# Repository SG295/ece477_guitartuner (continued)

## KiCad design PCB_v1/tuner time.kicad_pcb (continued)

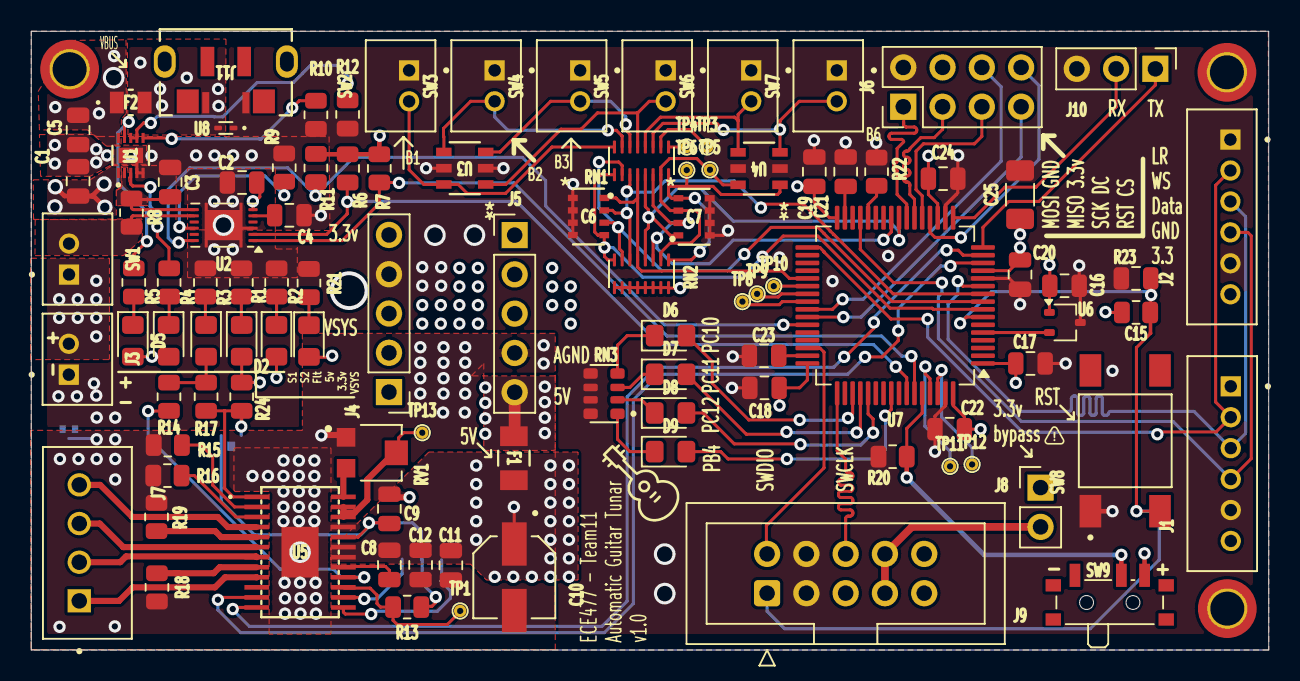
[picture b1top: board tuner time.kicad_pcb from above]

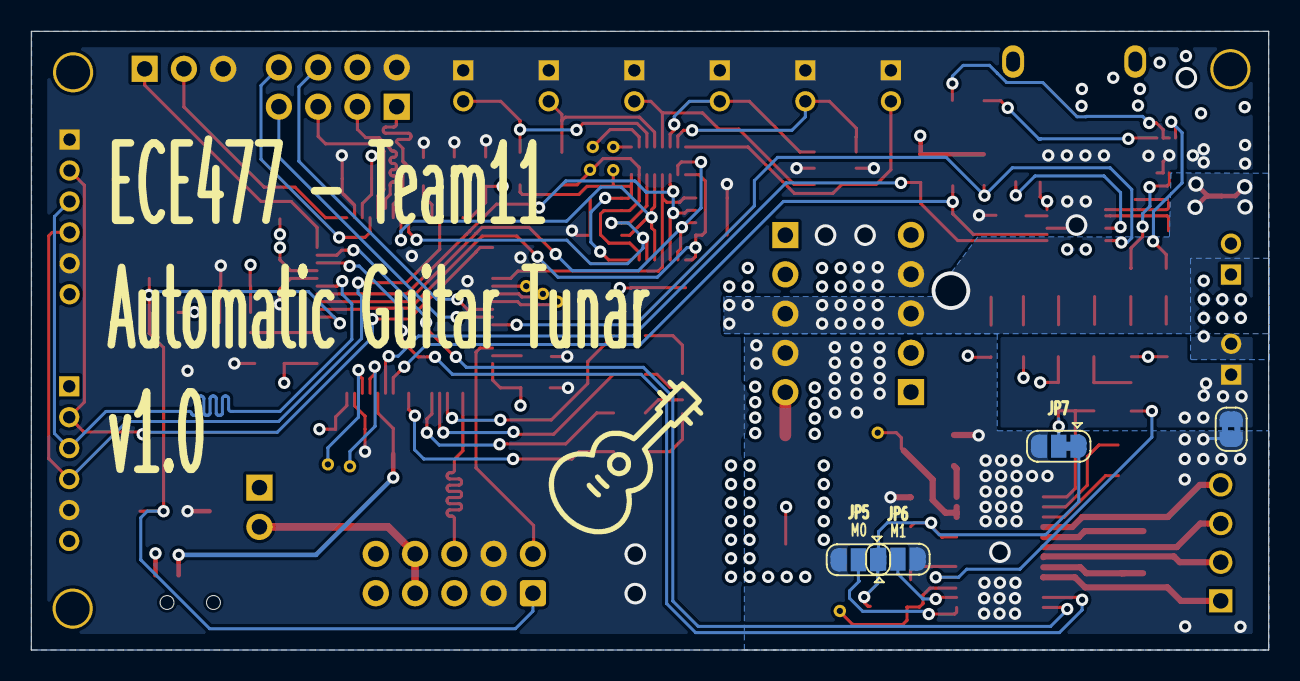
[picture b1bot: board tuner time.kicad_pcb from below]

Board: 4 copper layers, 80.0 x 40.0 mm, 109 parts (4 on the bottom side), 95 nets.

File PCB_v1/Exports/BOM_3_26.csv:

"Reference","Value","MFP","Qty","DNP","Description"
"C1,C3,C5","22uF","","3","","Unpolarized capacitor"
"C2","1uF","","1","","Unpolarized capacitor"
"C4","0.47uF","","1","","Unpolarized capacitor"
"C6,C7","100nF","CA0612KRX7R7BB104","2","",""
"C8","0.01uF","","1","","Unpolarized capacitor, small symbol"
"C9,C21,C23","2.2uF","","3","","-- mixed values --"
"C10","100uF","EEE1AA101WR","1","","Polarized capacitor, US symbol"
"C11,C17","10uF","","2","","-- mixed values --"
"C12","0.1uF","","1","","Unpolarized capacitor, small symbol"
"C15,C16,C18,C19,C20,C22,C24","100nF","","7","","Unpolarized capacitor"
"C25","1uF","TAJA105K016RNJ","1","","Polarized capacitor, US symbol"
"D1,D7","Orange","","2","","Light emitting diode"
"D2,D3,D6","Green","","3","","Light emitting diode"
"D4,D5,D8","Red","","3","","Light emitting diode"
"D9,D10","Blue","","2","","Light emitting diode"
"F1","C1F 2","C1F 2 (CA0612KRX7R7BB104)","1","",""
"F2","MFU0805FF01000P500","MFU0805FF01000P500","1","",""
"J1,J2","B6B-PH-K-S","B6B-PH-K-S","2","",""
"J3","JST_B2B-PH-K-S","S2B-PH-K-SLFSN","1","",""
"J4,J5","Conn_01x05_Pin","Genereic 5 pin 2.56mm","2","","Generic connector, single row, 01x05, script generated"
"J6","OLED Conn_02x04","Genereic 2x4 2.56 mm","1","","Generic connector, double row, 02x04, odd/even pin numbering scheme (row 1 odd numbers, row 2 even numbers), script generated (kicad-library-utils/schlib/autogen/connector/)"
"J7","B4B-XH-A","B4B-XH-A","1","",""
"J8","Conn_01x02_Pin","","1","","Generic connector, single row, 01x02, script generated"
"J9","Conn_02x05_Odd_Even","","1","","Generic connector, double row, 02x05, odd/even pin numbering scheme (row 1 odd numbers, row 2 even numbers), script generated (kicad-library-utils/schlib/autogen/connector/)"
"J10","Conn_01x03","Genereic 3 pin 2.56mm","1","","Generic connector, single row, 01x03, script generated (kicad-library-utils/schlib/autogen/connector/)"
"J11","1051640001","1051640001","1","",""
"R1,R2,R3,R4","680","","4","","-- mixed values --"
"R5,R21","1k","","2","","Resistor"
"R6,R7,R11","5.1k","","3","","Resistor"
"R8","0.01 1%","WSL0805R0100FEA1","1","","Resistor"
"R9,R10,R17,R20,R22,R23","10k","","6","-- mixed values --","-- mixed values --"
"R12","1.1k","","1","","Resistor"
"R13,R24","47k","","2","-- mixed values --","Resistor, US symbol"
"R14","1.5k","","1","","Resistor, US symbol"
"R15,R16","51k","","2","","Resistor, US symbol"
"R18,R19","0.10","WSTM0805QLR100FNR","2","","Resistor, US symbol"
"RN1","1k","EXB-2HV102JV","1","","8 resistor network, parallel topology, split"
"RN2","10k","EXB-2HV103JV","1","","8 resistor network, parallel topology, split"
"RN3","680","EXB-38V681JV","1","","4 resistor network, parallel topology, split"
"RV1","10k","TRIM_TC33X-2-103E","1","","Potentiometer, US symbol"
"SW1","SW_SPST","JST_B2B-PH-K-S","1","","Single Pole Single Throw (SPST) switch"
"SW2,SW3,SW4,SW5,SW6,SW7","SW_Push","JST_B2B-PH-K-S","6","","Push button switch, generic, two pins"
"SW8","SW_Push","TS04-66-65-BK-160-SMT","1","","Push button switch, generic, two pins"
"SW9","SW_SPDT","PCM12SMTR","1","","Switch, single pole double throw"
"TP1,TP8,TP9,TP10,TP11,TP12,TP13","~","N/A","7","","test point"
"TP3,TP4,TP5,TP6","TestPoint","N/A","4","","test point"
"U1","BQ25185DLHR","BQ25185DLHR","1","",""
"U2","BQ27441-G1","BQ27441-G1","1","","System Side Li Ion/Polymer Fuel Gauge, PDSON-12"
"U3,U4","SMS05T1G","SMS05T1G","2","",""
"U5","DRV8834PWP","DRV8834PWP","1","","11-V, 1.5-A,  dual H-bridge or stepper motor driver with 1/32 microstep indexer"
"U6","MAX7375AXR805","","1","","Silicon Clock Oscillator 8MHz, SC-70-3"
"U7","STM32F405RGTx","STM32F405RGT6","1","","STMicroelectronics Arm Cortex-M4 MCU, 1024KB flash, 192KB RAM, 168 MHz, 1.8-3.6V, 51 GPIO, LQFP64"
"U8","ESD9B5.0ST5G","ESD9B5.0ST5G","1","","ESD9B Series 7.8 V 15 pF Surface Mount TVS Diode - SOD-923"

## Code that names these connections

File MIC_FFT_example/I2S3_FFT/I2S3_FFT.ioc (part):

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Mcu.Name=STM32F407V(E-G)Tx
Mcu.Package=LQFP100
Mcu.UserName=STM32F407VGTx
PA0-WKUP.GPIOParameters=GPIO_PuPd,GPIO_Label,GPIO_ModeDefaultEXTI
PA0-WKUP.GPIO_Label=B1 [Blue PushButton]
PA0-WKUP.GPIO_ModeDefaultEXTI=GPIO_MODE_EVT_RISING
PA0-WKUP.GPIO_PuPd=GPIO_NOPULL
PA0-WKUP.Signal=GPXTI0
PA10.GPIOParameters=GPIO_Speed,GPIO_PuPd,GPIO_Label,GPIO_Mode
PA10.GPIO_Label=OTG_FS_ID
PA10.GPIO_Mode=GPIO_MODE_AF_PP
PA10.GPIO_PuPd=GPIO_NOPULL
PA10.GPIO_Speed=GPIO_SPEED_FREQ_LOW
PA10.Signal=USB_OTG_FS_ID
PA11.GPIOParameters=GPIO_Speed,GPIO_PuPd,GPIO_Label,GPIO_Mode
PA11.GPIO_Label=OTG_FS_DM
PA11.GPIO_Mode=GPIO_MODE_AF_PP
PA11.GPIO_PuPd=GPIO_NOPULL
PA11.GPIO_Speed=GPIO_SPEED_FREQ_LOW
PA11.Signal=USB_OTG_FS_DM
PA12.GPIOParameters=GPIO_Speed,GPIO_PuPd,GPIO_Label,GPIO_Mode
PA12.GPIO_Label=OTG_FS_DP
PA12.GPIO_Mode=GPIO_MODE_AF_PP
PA12.GPIO_PuPd=GPIO_NOPULL
PA12.GPIO_Speed=GPIO_SPEED_FREQ_LOW
PA12.Signal=USB_OTG_FS_DP
PA13.GPIOParameters=GPIO_Label
PA13.GPIO_Label=SWDIO
PA13.Mode=Serial_Wire
PA13.Signal=SYS_JTMS-SWDIO
PA14.GPIOParameters=GPIO_Label
PA14.GPIO_Label=SWCLK
PA14.Mode=Serial_Wire
PA14.Signal=SYS_JTCK-SWCLK
PA2.Mode=Asynchronous
PA2.Signal=USART2_TX
PA3.Mode=Asynchronous
PA3.Signal=USART2_RX
PA4.GPIOParameters=GPIO_Speed,GPIO_PuPd,GPIO_Label,GPIO_Mode
PA4.GPIO_Label=I2S3_WS [CS43L22_LRCK]
PA4.GPIO_Mode=GPIO_MODE_AF_PP
PA4.GPIO_PuPd=GPIO_NOPULL
PA4.GPIO_Speed=GPIO_SPEED_FREQ_LOW
PA4.Signal=I2S3_WS
PA5.GPIOParameters=GPIO_Speed,GPIO_PuPd,GPIO_Label,GPIO_Mode
PA5.GPIO_Label=SPI1_SCK [LIS302DL_SCL/SPC]
PA5.GPIO_Mode=GPIO_MODE_AF_PP
PA5.GPIO_PuPd=GPIO_NOPULL
PA5.GPIO_Speed=GPIO_SPEED_FREQ_LOW
PA5.Mode=Full_Duplex_Master
PA5.Signal=SPI1_SCK
PA6.GPIOParameters=GPIO_Speed,GPIO_PuPd,GPIO_Label,GPIO_Mode
PA6.GPIO_Label=SPI1_MISO [LIS302DL_SDO]
PA6.GPIO_Mode=GPIO_MODE_AF_PP
PA6.GPIO_PuPd=GPIO_NOPULL
PA6.GPIO_Speed=GPIO_SPEED_FREQ_LOW
PA6.Mode=Full_Duplex_Master
PA6.Signal=SPI1_MISO
PA7.GPIOParameters=GPIO_Speed,GPIO_PuPd,GPIO_Label,GPIO_Mode
PA7.GPIO_Label=SPI1_MOSI [LIS302DL_SDA/SDI/SDO]
PA7.GPIO_Mode=GPIO_MODE_AF_PP
PA7.GPIO_PuPd=GPIO_NOPULL
PA7.GPIO_Speed=GPIO_SPEED_FREQ_LOW
PA7.Mode=Full_Duplex_Master
PA7.Signal=SPI1_MOSI
PA9.GPIOParameters=GPIO_PuPd,GPIO_Label,GPIO_Mode
PA9.GPIO_Label=VBUS_FS
PA9.GPIO_Mode=GPIO_MODE_INPUT
PA9.GPIO_PuPd=GPIO_NOPULL
PA9.Signal=USB_OTG_FS_VBUS
PB1.GPIOParameters=GPIO_PuPd
PB1.GPIO_PuPd=GPIO_PULLDOWN
PB1.Signal=GPXTI1
PB10.GPIOParameters=GPIO_Speed,GPIO_PuPd,GPIO_Label,GPIO_Mode
PB10.GPIO_Label=CLK_IN [MP45DT02_CLK]
PB10.GPIO_Mode=GPIO_MODE_AF_PP
PB10.GPIO_PuPd=GPIO_NOPULL
PB10.GPIO_Speed=GPIO_SPEED_FREQ_LOW
PB10.Mode=Half_Duplex_Master
PB10.Signal=I2S2_CK
PB12.Mode=Half_Duplex_Master
PB12.Signal=I2S2_WS
PB2.Signal=GPIO_Input
PB3.GPIOParameters=GPIO_Label
PB3.GPIO_Label=SWO
PB3.Signal=SYS_JTDO-SWO
PB6.GPIOParameters=GPIO_Speed,GPIO_PuPd,GPIO_Label,GPIO_Pu,GPIO_Mode
PB6.GPIO_Label=Audio_SCL [CS43L22_SCL]
PB6.GPIO_Mode=GPIO_MODE_AF_OD
PB6.GPIO_Pu=GPIO_PULLUP
PB6.GPIO_PuPd=GPIO_NOPULL
PB6.GPIO_Speed=GPIO_SPEED_FREQ_LOW
PB6.Mode=I2C
PB6.Signal=I2C1_SCL
PB9.GPIOParameters=GPIO_Speed,GPIO_PuPd,GPIO_Label,GPIO_Pu,GPIO_Mode
PB9.GPIO_Label=Audio_SDA [CS43L22_SDA]
PB9.GPIO_Mode=GPIO_MODE_AF_OD
PB9.GPIO_Pu=GPIO_PULLUP
PB9.GPIO_PuPd=GPIO_NOPULL
PB9.GPIO_Speed=GPIO_SPEED_FREQ_LOW
PB9.Mode=I2C
PB9.Signal=I2C1_SDA
PC0.GPIOParameters=GPIO_Speed,PinState,GPIO_PuPd,GPIO_Label
PC0.GPIO_Label=OTG_FS_PowerSwitchOn
PC0.GPIO_PuPd=GPIO_NOPULL
PC0.GPIO_Speed=GPIO_SPEED_FREQ_LOW
PC0.PinState=GPIO_PIN_SET
PC0.Signal=GPIO_Output
PC10.GPIOParameters=GPIO_Speed,GPIO_PuPd,GPIO_Label,GPIO_Mode
PC10.GPIO_Label=I2S3_SCK [CS43L22_SCLK]
PC10.GPIO_Mode=GPIO_MODE_AF_PP
PC10.GPIO_PuPd=GPIO_NOPULL
PC10.GPIO_Speed=GPIO_SPEED_FREQ_LOW
PC10.Signal=I2S3_CK
PC12.GPIOParameters=GPIO_Speed,GPIO_PuPd,GPIO_Label,GPIO_Mode
PC12.GPIO_Label=I2S3_SD [CS43L22_SDIN]
PC12.GPIO_Mode=GPIO_MODE_AF_PP
PC12.GPIO_PuPd=GPIO_NOPULL
PC12.GPIO_Speed=GPIO_SPEED_FREQ_LOW
PC12.Signal=I2S3_SD
PC14-OSC32_IN.GPIOParameters=GPIO_Label
PC14-OSC32_IN.GPIO_Label=PC14-OSC32_IN
PC14-OSC32_IN.Mode=LSE-External-Oscillator
PC14-OSC32_IN.Signal=RCC_OSC32_IN
PC15-OSC32_OUT.GPIOParameters=GPIO_Label
PC15-OSC32_OUT.GPIO_Label=PC15-OSC32_OUT
PC15-OSC32_OUT.Mode=LSE-External-Oscillator
PC15-OSC32_OUT.Signal=RCC_OSC32_OUT
PC3.GPIOParameters=GPIO_Speed,GPIO_PuPd,GPIO_Label,GPIO_Mode
PC3.GPIO_Label=PDM_OUT [MP45DT02_DOUT]
PC3.GPIO_Mode=GPIO_MODE_AF_PP
PC3.GPIO_PuPd=GPIO_NOPULL
PC3.GPIO_Speed=GPIO_SPEED_FREQ_LOW
PC3.Mode=Half_Duplex_Master
PC3.Signal=I2S2_SD
PC7.GPIOParameters=GPIO_Speed,GPIO_PuPd,GPIO_Label,GPIO_Mode
PC7.GPIO_Label=I2S3_MCK [CS43L22_MCLK]
PC7.GPIO_Mode=GPIO_MODE_AF_PP
PC7.GPIO_PuPd=GPIO_NOPULL
PC7.GPIO_Speed=GPIO_SPEED_FREQ_LOW
PC7.Signal=I2S3_MCK
PD12.GPIOParameters=GPIO_Speed,GPIO_PuPd,GPIO_Label
PD12.GPIO_Label=LD4 [Green Led]
PD12.GPIO_PuPd=GPIO_NOPULL
PD12.GPIO_Speed=GPIO_SPEED_FREQ_LOW
PD12.Signal=GPIO_Output
PD13.GPIOParameters=GPIO_Speed,GPIO_PuPd,GPIO_Label
PD13.GPIO_Label=LD3 [Orange Led]
PD13.GPIO_PuPd=GPIO_NOPULL
PD13.GPIO_Speed=GPIO_SPEED_FREQ_LOW
PD13.Signal=GPIO_Output
PD14.GPIOParameters=GPIO_Speed,GPIO_PuPd,GPIO_Label
PD14.GPIO_Label=LD5 [Red Led]
PD14.GPIO_PuPd=GPIO_NOPULL
PD14.GPIO_Speed=GPIO_SPEED_FREQ_LOW
PD14.Signal=GPIO_Output
PD15.GPIOParameters=GPIO_Speed,GPIO_PuPd,GPIO_Label
PD15.GPIO_Label=LD6 [Blue Led]
PD15.GPIO_PuPd=GPIO_NOPULL
PD15.GPIO_Speed=GPIO_SPEED_FREQ_LOW
PD15.Signal=GPIO_Output
PD4.GPIOParameters=GPIO_Speed,GPIO_PuPd,GPIO_Label
PD4.GPIO_Label=Audio_RST [CS43L22_RESET]
PD4.GPIO_PuPd=GPIO_NOPULL
PD4.GPIO_Speed=GPIO_SPEED_FREQ_LOW
PD4.Signal=GPIO_Output
PD5.GPIOParameters=GPIO_PuPd,GPIO_Label,GPIO_Mode
PD5.GPIO_Label=OTG_FS_OverCurrent
PD5.GPIO_Mode=GPIO_MODE_INPUT
PD5.GPIO_PuPd=GPIO_NOPULL
PD5.Signal=GPIO_Input
PE3.GPIOParameters=GPIO_Speed,GPIO_PuPd,GPIO_Label
PE3.GPIO_Label=CS_I2C/SPI [LIS302DL_CS_I2C/SPI]
PE3.GPIO_PuPd=GPIO_NOPULL
PE3.GPIO_Speed=GPIO_SPEED_FREQ_LOW
PE3.Signal=GPIO_Output
PH0-OSC_IN.GPIOParameters=GPIO_Label
PH0-OSC_IN.GPIO_Label=PH0-OSC_IN
PH0-OSC_IN.Mode=HSE-External-Oscillator
PH0-OSC_IN.Signal=RCC_OSC_IN
PH1-OSC_OUT.GPIOParameters=GPIO_Label
PH1-OSC_OUT.GPIO_Label=PH1-OSC_OUT
PH1-OSC_OUT.Mode=HSE-External-Oscillator
PH1-OSC_OUT.Signal=RCC_OSC_OUT
RCC.HSE_VALUE=8000000
RCC.SYSCLKFreq_VALUE=160000000
RCC.SYSCLKSource=RCC_SYSCLKSOURCE_PLLCLK
board=STM32F407G-DISC1
boardIOC=true

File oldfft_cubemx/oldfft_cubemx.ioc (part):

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Mcu.Name=STM32F405RGTx
Mcu.Package=LQFP64
Mcu.UserName=STM32F405RGTx
PA2.Mode=Asynchronous
PA2.Signal=USART2_TX
PA3.Mode=Asynchronous
PA3.Signal=USART2_RX
PB10.Mode=Half_Duplex_Master
PB10.Signal=I2S2_CK
PB12.Mode=Half_Duplex_Master
PB12.Signal=I2S2_WS
PB4.Signal=GPIO_Output
PB6.Mode=I2C
PB6.Signal=I2C1_SCL
PB7.Mode=I2C
PB7.Signal=I2C1_SDA
PC10.Signal=GPIO_Output
PC11.Signal=GPIO_Output
PC12.Signal=GPIO_Output
PC3.Mode=Half_Duplex_Master
PC3.Signal=I2S2_SD
RCC.HSE_VALUE=25000000
RCC.SYSCLKFreq_VALUE=168000000
RCC.SYSCLKSource=RCC_SYSCLKSOURCE_PLLCLK
board=custom

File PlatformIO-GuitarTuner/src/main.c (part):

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void initb()
{
    RCC -> AHB1ENR |= RCC_AHB1ENR_GPIOBEN;
    GPIOB -> MODER &= ~0x30000; // Clear PB8
    GPIOB -> MODER |= 0x10000; // PB8 - Output

    GPIOB -> BSRR = (1 << 8); // Set PB8 High 
}

void initd()
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    RCC -> AHB1ENR |= RCC_AHB1ENR_GPIOCEN;
    RCC -> APB2ENR |= RCC_APB2ENR_SYSCFGEN; 

    GPIOC -> MODER &= ~0x3F3F; // Clear PC0-2 and PC4-6 to set as inputs
    GPIOC -> PUPDR &= ~0x3F3F; // Clear
    GPIOC -> PUPDR |= 0x1515; // Set to '01' for pull UP, have external, but extra sure line will be high

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    }
}
// Notes: 
//  I2C: PB6 (SCL) and PB7 (SDA) for Battery Management
//  SPI: CS - PA4, SCK - PA5, MISO - PA6, MOSI - PA7, DC - PA8, RST - PA9
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
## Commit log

2025-02-10 Initial push of PlatformIO project
2025-02-10 WIP, writing driver library
2025-02-10 added testing flags for old demo code
2025-02-11 small change to header file
2025-02-11 Adding SRC folder main branch was lacking w/ template main
2025-02-11 initial commit for battery branch
2025-02-11 OLED initalization and clear screen working!
2025-02-12 Able to display text following 362 protocol.
2025-02-22 Adding the FFT Example
2025-02-22 Adding the Python script
2025-02-26 adding the mic schematic
2025-02-26 Adding mic PCB
2025-02-26 Schematic initial multipart
2025-02-26 adding the parts library
2025-02-26 pcb updated
2025-02-26 Demo UI with buttons
2025-03-01 Updated power schematic :D
2025-03-01 Updated UI w/ new header for OLED and updated MCU w/ STM32F405 and SWD (also some code I accdientally modified on this branch)
2025-03-01 Last push before PCB
2025-03-01 changed the MICs to JST headers
2025-03-01 changed debouncing order, switches to jst, and array resistors
2025-03-02 PCB changes before changing Seth's clock
2025-03-02 Update before adding AGND for the power delivery
2025-03-02 Initial placement draft
2025-03-03 PCB updates
2025-03-04 updated the schematic only
2025-03-04 bringing back the PCB to Life
2025-03-04 adjusted placments
2025-03-04 Main routes done, no power planes, no DRC
2025-03-08 Buttons working w/ interrupts - need to fix bouncing issue again
2025-03-09 Power Layout done
2025-03-10 before annonation reset
2025-03-10 pushing BOM
2025-03-12 adding the libraries and the new bom for footprint
2025-03-12 adding the crystal
2025-03-12 added the footprints
2025-03-13 before oscilator
2025-03-13 add before moving to lab computer
2025-03-13 added the oscilator
2025-03-13 push for jtag fix
2025-03-13 added arrow drawing
2025-03-13 Updated debug connection on MCU
2025-03-13 fixed small bug w/ arrow
2025-03-14 before major move
2025-03-14 Placement done
2025-03-14 placment is done now I swear
2025-03-14 before DRC
2025-03-14 done no text before stiching via
2025-03-14 routing done no silkscreen
2025-03-15 PCB all Done no Dr.Walter Review
2025-03-23 small modification for framework of entire system
2025-03-26 last PCB
2025-03-28 Added image display and started working on battery management I2C
2025-03-30 I2C working
2025-04-02 creation of files
2025-04-02 Working battery IC interaction :)
2025-04-03 motor code added and working
2025-04-03 Motor spins now
2025-04-03 drive_motor_rpm() created
2025-04-03 step_motor()
2025-04-07 Held button functionality working and larger font
2025-04-09 fixed u8 issue & set platform to PCB
2025-04-10 PCB style checkoff
2025-04-11 Demo for battery IC
2025-04-11 Mic work and battery demo
2025-04-16 Huge UI update
2025-04-17 PCB final
2025-04-17 Adding the CMSIS Mic
2025-04-18 UI mostly done, waiting for mic + slight motor RPM tweak
2025-04-18 Reorganized code into proper libraries for each componenet and adding some flags for testing w/ or w/o certain components
2025-04-18 Old Tarcer
2025-04-20 Added DMA to mic
2025-04-22 lot of work on mic, added DSP library and am getting results...not sure if they're right though
2025-04-23 WIP adding UART
2025-04-23 small changes to mic code and added priorities for interrupts
2025-04-23 Added TIM4 and TIM3 interrupts 4 freespin purposes
2025-04-23 free spin
2025-04-23 free spin should work better now
2025-04-23 fixed drive_motor()
2025-04-23 fixed variable type for drive_motor() from u8
2025-04-23 lengthened free spin time
2025-04-24 mic NOT working but DMA tweak...might be cooked :O
2025-04-24 FFT works for 32k
2025-04-24 512 fft
2025-04-24 closer to the end
2025-04-24 cleaning it up
2025-04-24 The FFT workes for a better range
2025-04-24 with max print
2025-04-24 top 10 working
2025-04-24 The FFT working very well, harmonics still there
2025-04-24 double mic working
2025-04-24 variable name change
2025-04-24 ported CMSIS code over to integrate
2025-04-24 adding i2c and interpolation
2025-04-24 FIXED BATTERY LSFG
2025-04-24 mic rough draft
2025-04-24 WIP button motor feedback loop
2025-04-25 VERY CLOSE TO WORKING \(^-^)/
2025-04-25 Finished product...good job team
2025-05-03 removed unecessary files and renamed folder
2025-05-03 cleaning up
